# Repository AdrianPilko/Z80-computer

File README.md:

# Z80 computer
 A minimal z80 computer with keypad input and 2line dot matrix display output

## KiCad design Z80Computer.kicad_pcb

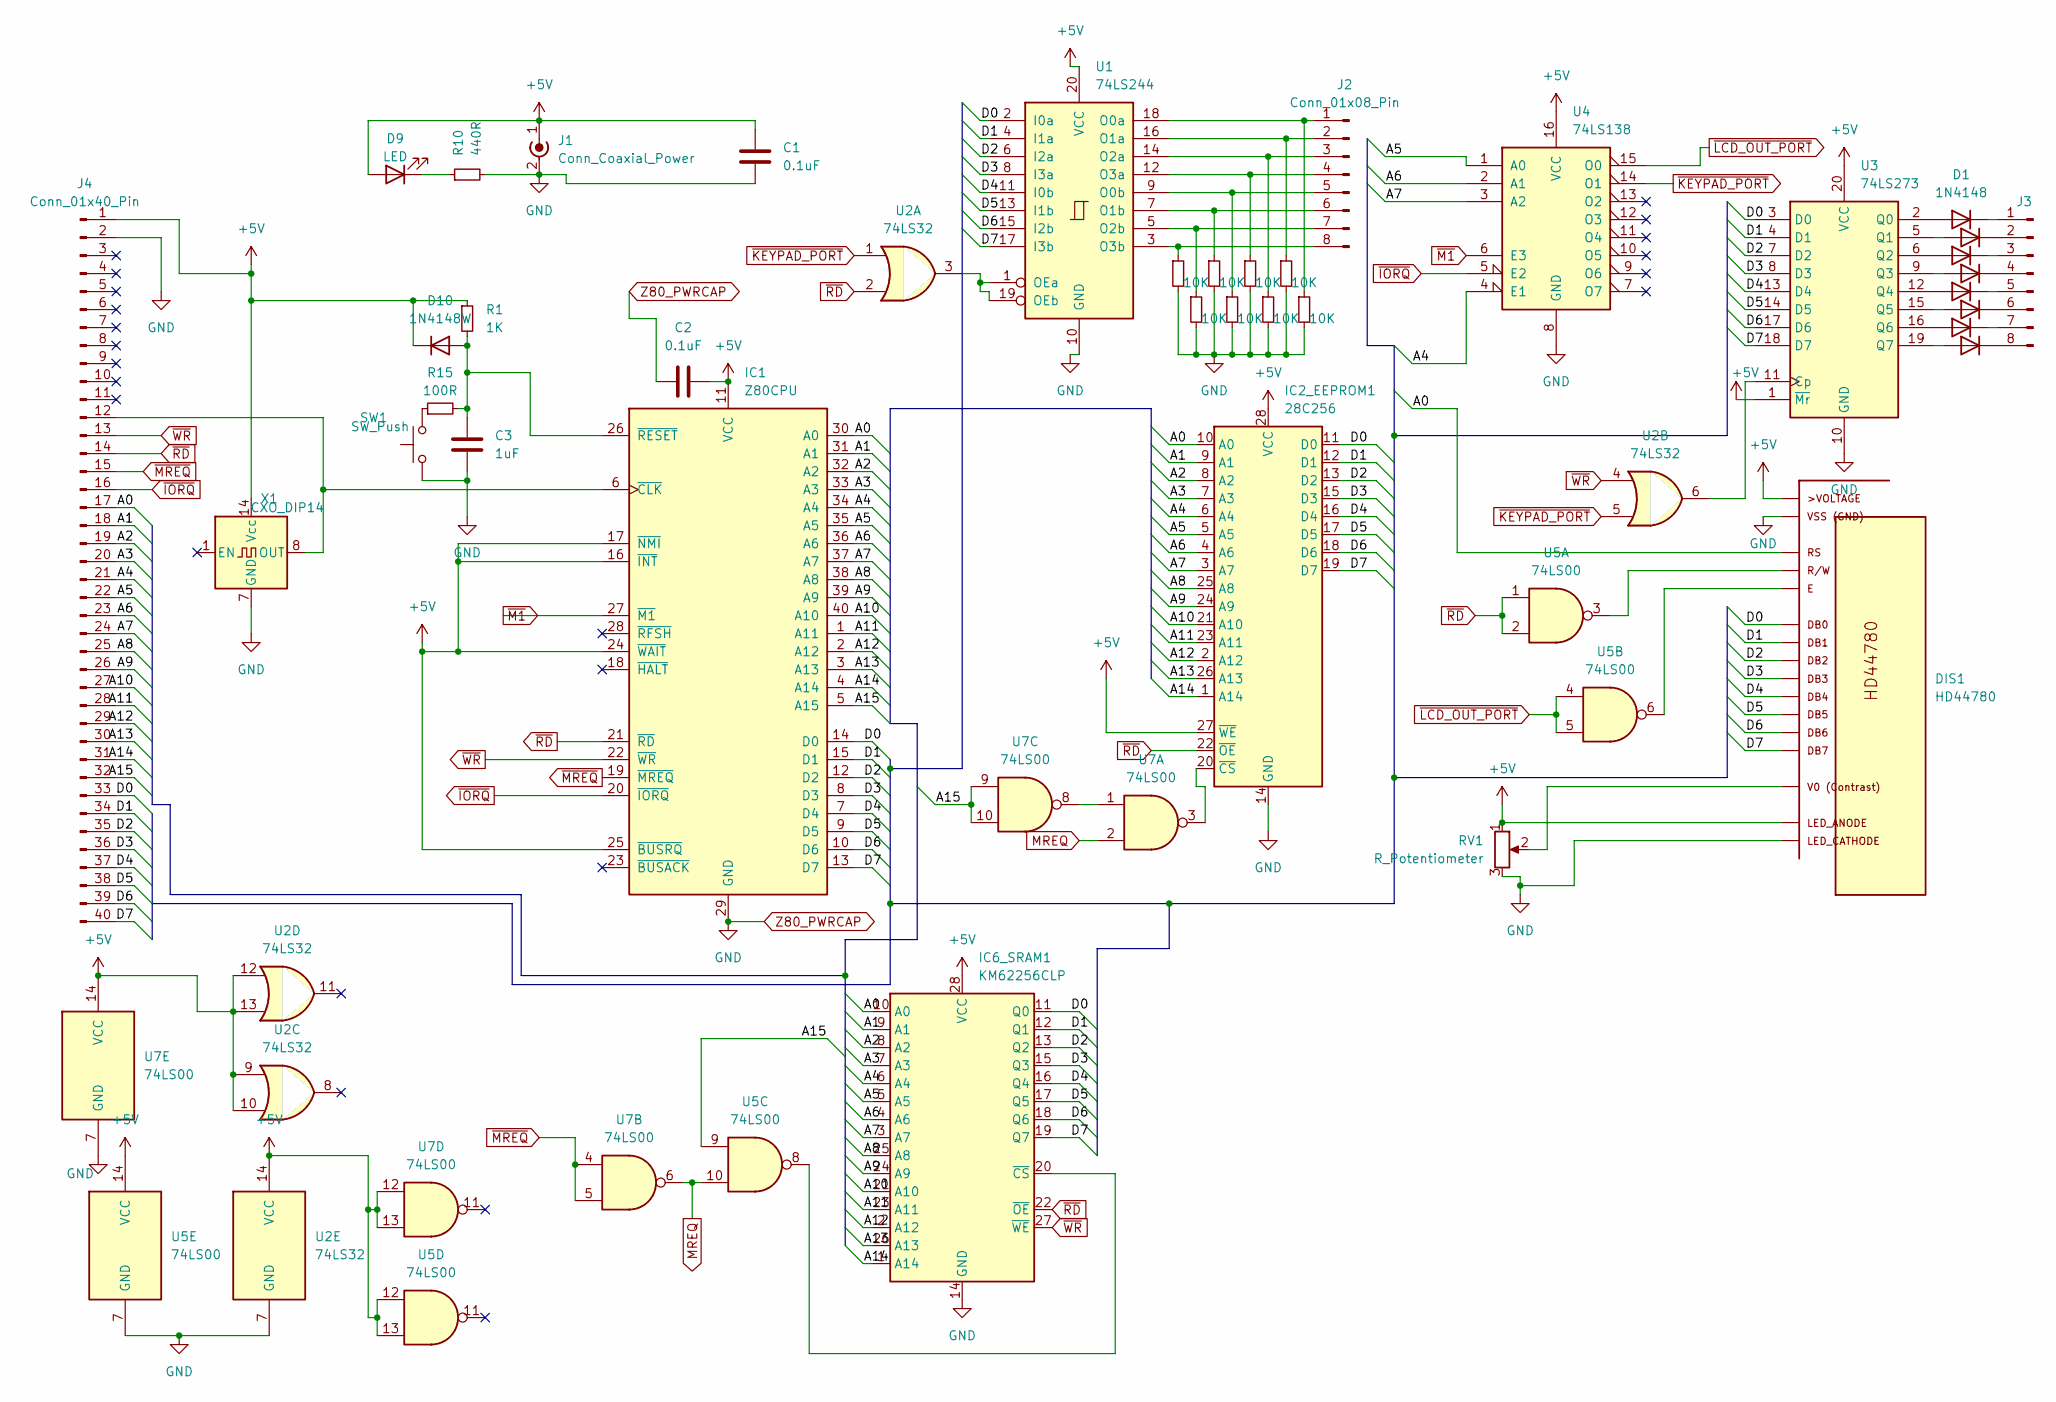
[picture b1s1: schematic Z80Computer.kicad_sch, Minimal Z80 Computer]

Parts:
C1, C2: 0.1uF; CP_Radial_D4.0mm_P1.50mm
C3: 1uF; CP_Axial_L10.0mm_D4.5mm_P15.00mm_Horizontal
D1, D2, D3, D4, D5, D6, D7, D8: 1N4148; D_DO-35_SOD27_P7.62mm_Horizontal
D9: LED; LED_D5.0mm
D10: 1N4148W; D_SOD-123
DIS1: HD44780; 16026-16X2; VOLTAGE 5V
IC1: Z80CPU; DIP-40_W15.24mm
IC2_EEPROM1: 28C256; DIP-28_W15.24mm
IC6_SRAM1: KM62256CLP; DIP-28_W15.24mm
J1: Conn_Coaxial_Power; SMA_Amphenol_901-143_Horizontal
J2, J3: Conn_01x08_Pin; JST_EH_B8B-EH-A_1x08_P2.50mm_Vertical
J4: Conn_01x40_Pin; Samtec_MECF-40-0_-NP-L-DV_2x40_P1.27mm_Edge
R1: 1K; R_Axial_DIN0204_L3.6mm_D1.6mm_P1.90mm_Vertical
R2, R3, R4, R5, R6, R7, R8, R9: 10K; R_Axial_DIN0204_L3.6mm_D1.6mm_P1.90mm_Vertical
R10: 440R; R_Axial_DIN0204_L3.6mm_D1.6mm_P1.90mm_Vertical
R15: 100R; R_Axial_DIN0204_L3.6mm_D1.6mm_P1.90mm_Vertical
RV1: R_Potentiometer; Potentiometer_ACP_CA6-H2,5_Horizontal
SW1: SW_Push; KSA_Tactile_SPST
U1: 74LS244; DIP-20_W7.62mm
U2: 74LS32; DIP-14_W7.62mm
U3: 74LS273; DIP-20_W7.62mm
U4: 74LS138; DIP-16_W7.62mm
U5, U7: 74LS00; DIP-14_W7.62mm
X1: CXO_DIP14; Oscillator_DIP-14

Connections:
+5V: C1.1, C2.2, D9.2 (A), D10.1 (K), DIS1.P$2, DIS1.P$15, IC1.11 (VCC), IC1.16 (~INT), IC1.17 (~NMI), IC1.24 (~WAIT), IC1.25 (~BUSRQ), IC2_EEPROM1.27 (~WE), IC2_EEPROM1.28 (VCC), IC6_SRAM1.28 (VCC), J1.1 (In), J4.1, R1.1, RV1.1, U1.20 (VCC), U2.9, U2.10, U2.12, U2.13, U2.14 (VCC), U3.1 (~Mr), U3.20 (VCC), U4.16 (VCC), U5.12, U5.13, U5.14 (VCC), U7.12, U7.13, U7.14 (VCC), X1.14 (Vcc); also elsewhere on the board
/A0: DIS1.P$4, IC1.30 (A0), IC2_EEPROM1.10 (A0), IC6_SRAM1.10 (A0), J4.17
/A1: IC1.31 (A1), IC2_EEPROM1.9 (A1), IC6_SRAM1.9 (A1), J4.18
/A2: IC1.32 (A2), IC2_EEPROM1.8 (A2), IC6_SRAM1.8 (A2), J4.19
/A3: IC1.33 (A3), IC2_EEPROM1.7 (A3), IC6_SRAM1.7 (A3), J4.20
/A4: IC1.34 (A4), IC2_EEPROM1.6 (A4), IC6_SRAM1.6 (A4), J4.21, U4.4 (E1)
/A5: IC1.35 (A5), IC2_EEPROM1.5 (A5), IC6_SRAM1.5 (A5), J4.22, U4.1 (A0)
/A6: IC1.36 (A6), IC2_EEPROM1.4 (A6), IC6_SRAM1.4 (A6), J4.23, U4.2 (A1)
/A7: IC1.37 (A7), IC2_EEPROM1.3 (A7), IC6_SRAM1.3 (A7), J4.24, U4.3 (A2)
/A8: IC1.38 (A8), IC2_EEPROM1.25 (A8), IC6_SRAM1.25 (A8), J4.25
/A9: IC1.39 (A9), IC2_EEPROM1.24 (A9), IC6_SRAM1.24 (A9), J4.26
/A10: IC1.40 (A10), IC2_EEPROM1.21 (A10), IC6_SRAM1.21 (A10), J4.27
/A11: IC1.1 (A11), IC2_EEPROM1.23 (A11), IC6_SRAM1.23 (A11), J4.28
/A12: IC1.2 (A12), IC2_EEPROM1.2 (A12), IC6_SRAM1.2 (A12), J4.29
/A13: IC1.3 (A13), IC2_EEPROM1.26 (A13), IC6_SRAM1.26 (A13), J4.30
/A14: IC1.4 (A14), IC2_EEPROM1.1 (A14), IC6_SRAM1.1 (A14), J4.31
/A15: IC1.5 (A15), J4.32, U5.9, U7.9, U7.10
/D0: DIS1.P$7, IC1.14 (D0), IC2_EEPROM1.11 (D0), IC6_SRAM1.11 (Q0), J4.33, U1.2 (I0a), U3.3 (D0); also elsewhere on the board
/D1: DIS1.P$8, IC1.15 (D1), IC2_EEPROM1.12 (D1), IC6_SRAM1.12 (Q1), J4.34, U1.4 (I1a), U3.4 (D1); also elsewhere on the board
/D2: DIS1.P$9, IC1.12 (D2), IC2_EEPROM1.13 (D2), IC6_SRAM1.13 (Q2), J4.35, U1.6 (I2a), U3.7 (D2); also elsewhere on the board
/D3: DIS1.P$10, IC1.8 (D3), IC2_EEPROM1.15 (D3), IC6_SRAM1.15 (Q3), J4.36, U1.8 (I3a), U3.8 (D3); also elsewhere on the board
/D4: DIS1.P$11, IC1.7 (D4), IC2_EEPROM1.16 (D4), IC6_SRAM1.16 (Q4), J4.37, U1.11 (I0b), U3.13 (D4); also elsewhere on the board
/D5: DIS1.P$12, IC1.9 (D5), IC2_EEPROM1.17 (D5), IC6_SRAM1.17 (Q5), J4.38, U1.13 (I1b), U3.14 (D5); also elsewhere on the board
/D6: DIS1.P$13, IC1.10 (D6), IC2_EEPROM1.18 (D6), IC6_SRAM1.18 (Q6), J4.39, U1.15 (I2b), U3.17 (D6); also elsewhere on the board
/D7: DIS1.P$14, IC1.13 (D7), IC2_EEPROM1.19 (D7), IC6_SRAM1.19 (Q7), J4.40, U1.17 (I3b), U3.18 (D7); also elsewhere on the board
MREQ: U5.10, U7.2, U7.6
unnamed: D1.2 (A), U3.2 (Q0)
unnamed: D1.1 (K), J3.1
unnamed: D2.2 (A), U3.9 (Q3)
unnamed: D2.1 (K), J3.4
unnamed: D3.2 (A), U3.6 (Q2)
unnamed: D3.1 (K), J3.3
unnamed: D4.2 (A), U3.12 (Q4)
unnamed: D4.1 (K), J3.5
unnamed: D5.2 (A), U3.16 (Q6)
unnamed: D5.1 (K), J3.7
unnamed: D6.2 (A), U3.15 (Q5)
unnamed: D6.1 (K), J3.6
unnamed: D7.2 (A), U3.19 (Q7)
unnamed: D7.1 (K), J3.8
unnamed: D8.2 (A), U3.5 (Q1)
unnamed: D8.1 (K), J3.2
unnamed: D9.1 (K), R10.1
unnamed: C3.1, D10.2 (A), IC1.26 (~RESET), R1.2, R15.2
unnamed: DIS1.P$3, RV1.2
unnamed: DIS1.P$5, U5.3
unnamed: DIS1.P$6, U5.6
unnamed: IC1.6 (~CLK), J4.12, X1.8 (OUT)
unnamed: IC2_EEPROM1.20 (~CS), U7.3
unnamed: IC6_SRAM1.20 (~CS), U5.8
unnamed 50: J2.1, R9.1, U1.18 (O0a); also elsewhere on the board
unnamed 51: J2.2, R8.1, U1.16 (O1a); also elsewhere on the board
unnamed 52: J2.3, R7.1, U1.14 (O2a); also elsewhere on the board
unnamed 53: J2.4, R6.1, U1.12 (O3a); also elsewhere on the board
unnamed 54: J2.5, R5.1, U1.9 (O0b); also elsewhere on the board
unnamed 55: J2.6, R3.1, U1.7 (O1b); also elsewhere on the board
unnamed 56: J2.7, R4.1, U1.5 (O2b); also elsewhere on the board
unnamed 57: J2.8, R2.1, U1.3 (O3b); also elsewhere on the board
unnamed: R15.1, SW1.2
unnamed 63: U1.1 (OEa), U1.19 (OEb), U2.3; also elsewhere on the board
unnamed: U2.6, U3.11 (Cp)
unnamed: U7.1, U7.8
Z80_PWRCAP: C1.2, C2.1, C3.2, DIS1.P$1, DIS1.P$16, IC1.29 (GND), IC2_EEPROM1.14 (GND), IC6_SRAM1.14 (GND), J1.2 (Ext), J4.2, R2.2, R3.2, R4.2, R5.2, R6.2, R7.2, R8.2, R9.2, R10.2, RV1.3, SW1.1, U1.10 (GND), U2.7 (GND), U3.10 (GND), U4.8 (GND), U5.7 (GND), U7.7 (GND), X1.7 (GND); also elsewhere on the board
~IORQ: IC1.20 (~IORQ), J4.16, U4.5 (E2)
~KEYPAD_PORT: U2.1, U2.5, U4.14 (O1)
~LCD_OUT_PORT: U4.15 (O0), U5.4, U5.5
~M1: IC1.27 (~M1), U4.6 (E3)
~MREQ: IC1.19 (~MREQ), J4.15, U7.4, U7.5
~RD: IC1.21 (~RD), IC2_EEPROM1.22 (~OE), IC6_SRAM1.22 (~OE), J4.14, U2.2, U5.1, U5.2
~WR: IC1.22 (~WR), IC6_SRAM1.27 (~WE), J4.13, U2.4

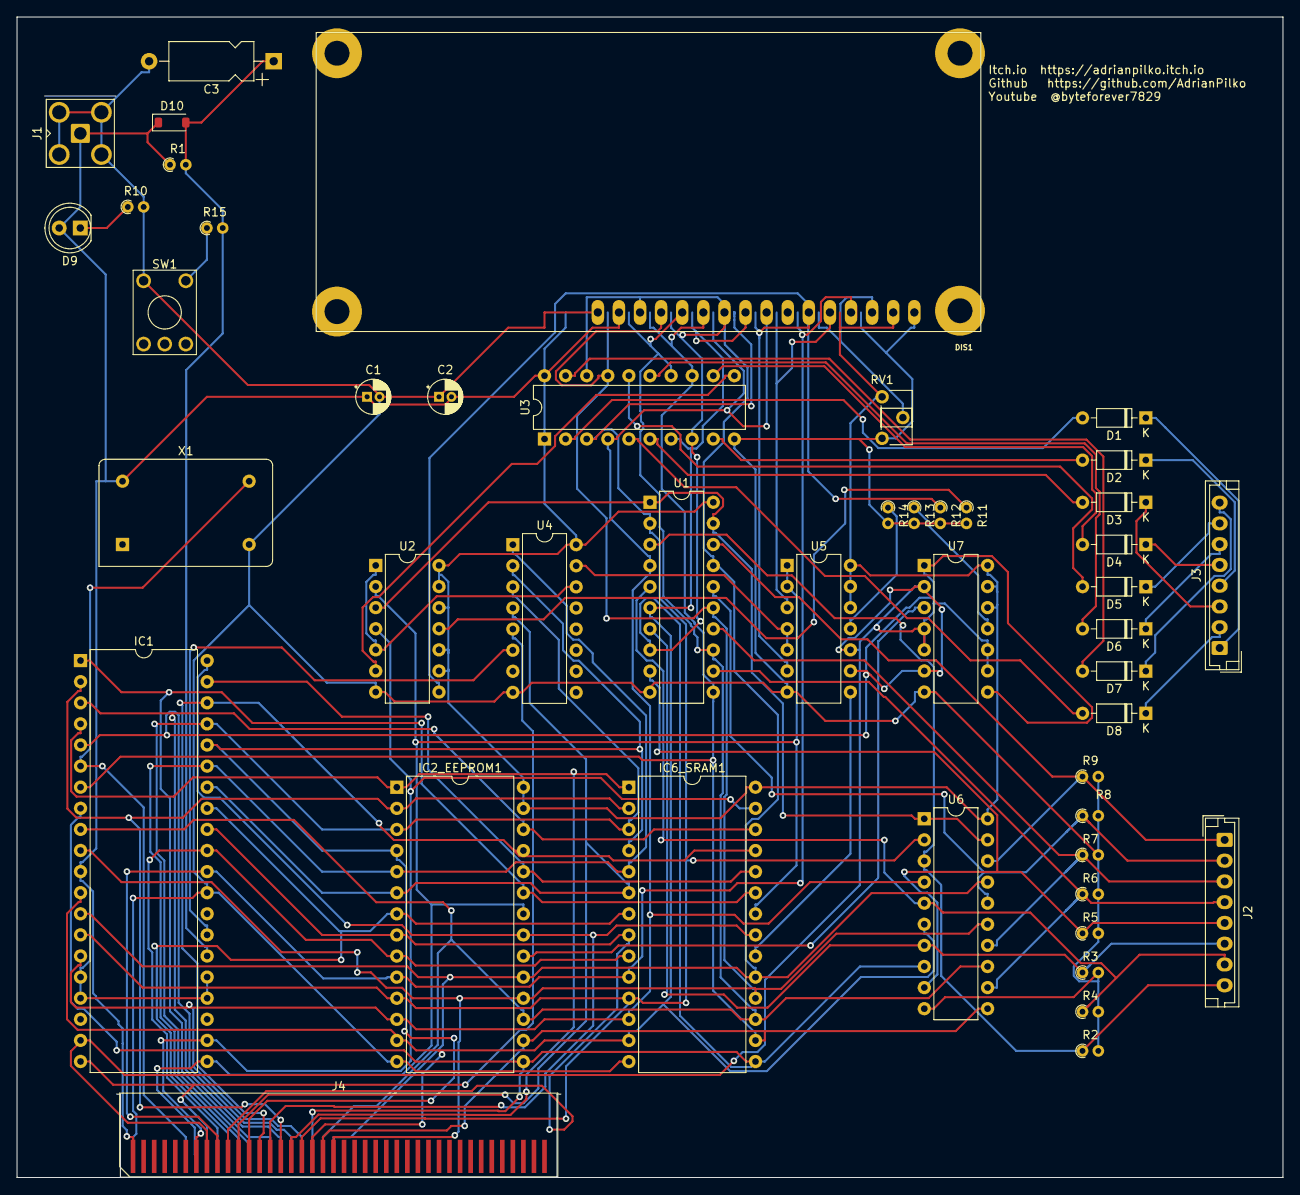
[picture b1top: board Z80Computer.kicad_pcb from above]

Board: 2 copper layers, 152.4 x 139.7 mm, 46 parts (0 on the bottom side), 70 nets.

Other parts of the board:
R11, R12, R13, R14: 10K; R_Axial_DIN0204_L3.6mm_D1.6mm_P1.90mm_Vertical
U6: 74LS244; DIP-20_W7.62mm

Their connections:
+5V: U6.20 (VCC); also elsewhere on the board
/D0: U6.2 (I0a); also elsewhere on the board
/D1: U6.4 (I1a); also elsewhere on the board
/D2: U6.6 (I2a); also elsewhere on the board
/D3: U6.8 (I3a); also elsewhere on the board
/D4: U6.11 (I0b); also elsewhere on the board
/D5: U6.13 (I1b); also elsewhere on the board
/D6: U6.15 (I2b); also elsewhere on the board
/D7: U6.17 (I3b); also elsewhere on the board
unnamed 50: U6.18 (O0a); also elsewhere on the board
unnamed 51: U6.16 (O1a); also elsewhere on the board
unnamed 52: U6.14 (O2a); also elsewhere on the board
unnamed 53: U6.12 (O3a); also elsewhere on the board
unnamed 54: U6.9 (O0b); also elsewhere on the board
unnamed 55: U6.7 (O1b); also elsewhere on the board
unnamed 56: U6.5 (O2b); also elsewhere on the board
unnamed 57: U6.3 (O3b); also elsewhere on the board
unnamed 63: U6.1 (OEa), U6.19 (OEb); also elsewhere on the board
Z80_PWRCAP: R11.2, R12.2, R13.2, R14.2, U6.10 (GND); also elsewhere on the board

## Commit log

2023-10-30 initial layout schematic and lib created
2023-10-30 added more components
2023-11-03 got most of the circuit done apart from key pad
2023-11-04 before auto route pcb
2023-11-04 Added text
2023-11-04 autorouted
2023-11-04 added Gerber files
2023-11-04 reworked to correct z80 footprint
2023-11-05 updated zip file
2023-11-05 Added RC reset and fixed RAM ROM chip select
2023-11-06 added some footprints and updated pcb
2023-12-17 deleted backups
2023-12-17 dodge game code added
2023-12-17 galaxy moves left on row one star moves right
2023-12-17 random galaxy row control star with keypad
2023-12-17 fixes for schematic (not redone PCB layout though
2023-12-18 added simple score printed after game over
2024-12-23 various updates to 40by20 display
2024-12-23 built row 2 works
2024-12-23 all 4 rows now work in test mode
2024-12-26 first attempt at input from arduino
2024-12-28 keyboard input working reliably
    next step is to add more logic into z80 code to execute commands like clear display and to properly go to next line
2024-12-28 basic test to lcd working
    still can't get the row selection working properly
2024-12-29 text typed on PC terminal into arduino appear on lcd properly
2024-12-29 carridge return on lcd and started command interpreter
2024-12-31 started on a bootloader so don't have to keep swapping eeproms
2024-12-31 got to the point where it will load code and run
    included two short programs one to display hash then halt another to display dollar
2024-12-31 added hello program and increase arduino buffer
2024-12-31 added hello wolrd using rom code
2025-01-01 added ability to change address to store at
2025-01-01 minor fixes plus happy new year easter egg
